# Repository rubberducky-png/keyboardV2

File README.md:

# keyboardV2: compact 61-key keyboard

A fully custom 61-key mechanical keyboard designed by me, including the PCB, case, firmware, and assembly.

Started With the Macondo Program and Finished with the Forge Program

## Features

- Custom PCB designed from scratch
- Hot-swappable MX-compatible switches
- ZMK firmware
- Screw-in stabilizers
- 3D printed two-piece tray mount case
- Switch plate
- PCB foam
- bluetooth
- RGB lights
  
## Why I Built It

I built another keyboard before this and ended up hating how it looked and how I desgined it. So I went back to the drawing board and decided to make one I would actually like.

## Design Process

The project began by selecting a 61-key layout that has a lot of function but is also on the smaller side. I then designed the PCB in KiCad, routed all the traces, and added support for hot-swap sockets and USB-C connectivity. After the electronics were complete I designed a simple tray mount in Onshape. The case is made out of two PLA printed pieces and includes a shelf for the pcb to rest on. Because of small bed size I will have to print them in pieces.

Finally, the keyboard will be flashed with VIA firmware

## Challenges

Some of the biggest challenges included:

- Learning PCB routing and keyboard matrix design
- Designing a printable case that was able to support the pcb well
- Ensuring all mounting points aligned correctly

## Images and Renders!

### Matrix Schematic

### OnShape Render
- assembly file is public at: https://cad.onshape.com/documents/9cbec0f54e40138e58fcc79a/w/808f2acb50a46c5c63af6f12/e/cd5daac02ca5b9e828f3d085

#### Case

### Switch Plate

### PCB

### Assembly

## Bill of Materials (BOM)

The following table lists the components required to build the custom 60% wireless mechanical keyboard.

| # | Component | Description | Quantity | Unit Price | Subtotal |
|---:|---|---|---:|---:|---:|
| 1 | [Glorious Fox Linear Switches](https://www.amazon.com/GLORIOUS-Linear-Mechanical-Switches-Keyboards/dp/B0D7QW8SQ9) | MX-compatible linear switches, 110-pack | 110 | $0.2272 | $24.99 |
| 2 | [Gateron PCB-Mounted Stabilizers](https://www.amazon.com/gp/product/B0BZYK3X1S) | PCB-mounted stabilizer set for larger keys | 1 set | $9.99 | $9.99 |
| 3 | [SuperMini nRF52840](https://www.amazon.com/AITRIP-Development-Bluetooth-Management-Module%EF%BC%8CNano/dp/B0DCZJKYL1) | Pro Micro alternative; Bluetooth LE and ZMK compatible | 1 | $13.99 | $13.99 |
| 4 | [SK6812MINI-E RGB LEDs](https://www.amazon.com/100PCS-Similar-WS2812B-Individually-Addressable/dp/B0DMNBBM9V) | Individually addressable per-key RGB LEDs, 100-pack | 100 | $0.15 | $15.46 |
| 5 | [Kailh Hot-Swap Sockets](https://www.amazon.com/Hot-swappable-Socket-CPG151101S11-Mechanical-Keyboard/dp/B096WZ6TJ5) | MX-compatible hot-swap sockets, 100-pack | 100 | $0.125 | $12.50 |
| 6 | [JLCPCB PCB Fabrication](https://jlcpcb.com) | Custom PCB manufacturing, 5 boards, including shipping | 1 order | — | $35.03 |
| 7 | [3.7V LiPo Battery](https://www.amazon.com/YTKavq-Battery-Lithium-Rechargeable-Connector/dp/B08TV4J9H7) | Rechargeable lithium polymer battery, approximately 1000mAh, JST-PH connector | 1 | $7.59 | $7.59 |
| 8 | [JST-PH 2.0mm Connector](https://www.amazon.com/JST-PH-Connector-Silicone-Cables-Female/dp/B0F9PD2LPW) | 2-pin battery connector with silicone wiring | 1 | $5.99 | $5.99 |
| 9 | [SPDT Slide Switch](https://www.amazon.com/gp/product/B0DN67RV4W) | Power on/off switch, 2.54mm pin spacing | 1 | $6.99 | $6.99 |
| 10 | [Momentary Tactile Push Button](https://www.amazon.com/Momentary-Tactile-Switches-Through-Breadboard/dp/B0G5Q9RPJW) | Reset button | 1 | $5.99 | $5.99 |
| 11 | [Womier Double-Shot PBT Keycaps](https://www.amazon.com/Keycaps-Doubleshot-Percent-Mechanical-Keyboard/dp/B0DDC6PNY6) | Cherry-profile double-shot PBT keycap set | 1 set | $17.99 | $17.99 |
| 12 | [22µF 0805 MLCC Capacitors](https://www.amazon.com/Chip-Capacitor-MLCC-22uF-CS2012X5R226M250NRE/dp/B096WDCLWY) | X5R ceramic capacitors for power filtering, 10-pack | 10 | $0.499 | $4.99 |
| 13 | [CHANZON 100nF 0805 Capacitors](https://www.amazon.com/CHANZON-100nF-Ceramic-Capacitor-100pcs/dp/B0GWH4RRQS) | LED decoupling capacitors, 100-pack | 100 | $0.076 | $7.60 |
| 14 | [0805 SMD Resistors 470 ohms](https://www.amazon.com/HiLetgo-Values-Resistors-Assortment-Resistor/dp/B07R5S5RFK/ref=sr_1_1_sspa?dib=eyJ2IjoiMSJ9.QrbL5hsl3y3O6gmstmy_4ZD0PpMRLFJ7NhmAE3dIEMUj69VnxSscBgx1Y_NvgiuXhPPsI573Q7wFUPvs_THPc2HkjAqAmswXhBcCxd4afR0o-SfQNniGOnE40pkLAjc971XgZG_Vreq0zhsYtezMDwFAChPOIei81v4d8d9fdSgrF1oYQbbqwz3Tw8FshrM3dyWXSGyEhGIDRhhHlnimh7bHPPrxl0DcY0hEvuhDMCE.ricUM_RpbJ0mivxPTOZyA8MBNaog89FuJmiqJ4fPW4c&dib_tag=se&keywords=450+ohm+0805+SMD+resistor&qid=1794352900&sr=8-1-spons&sp_csd=d2lkZ2V0TmFtZT1zcF9hdGY&psc=1) | 0805 resistors, 400 pack | 400 | | $6.89

### Cost Summary

| Category | Cost |
|---|---:|
| Components and hardware | $140.96 |
| PCB fabrication and shipping | $35.03 |
| **Total Project Cost** | **$175.99** |

*Prices are based on the listed purchase prices and may change. The PCB cost includes manufacturing and shipping.*

### Project Notes
- Keyboard layout: 60% ANSI.
- Connectivity: Bluetooth Low Energy (BLE).
- Firmware: ZMK.
- Switch compatibility: Cherry MX-style mechanical switches.
- Switch mounting: MX hot-swap sockets.
- Lighting: Individually addressable per-key RGB using SK6812MINI-E LEDs.
- Battery: Rechargeable 3.7V lithium polymer cell.
- Layers: Two firmware layers, with Right Alt configured as the Fn key.

## Shoutout hackclub and the macondo program

</center>

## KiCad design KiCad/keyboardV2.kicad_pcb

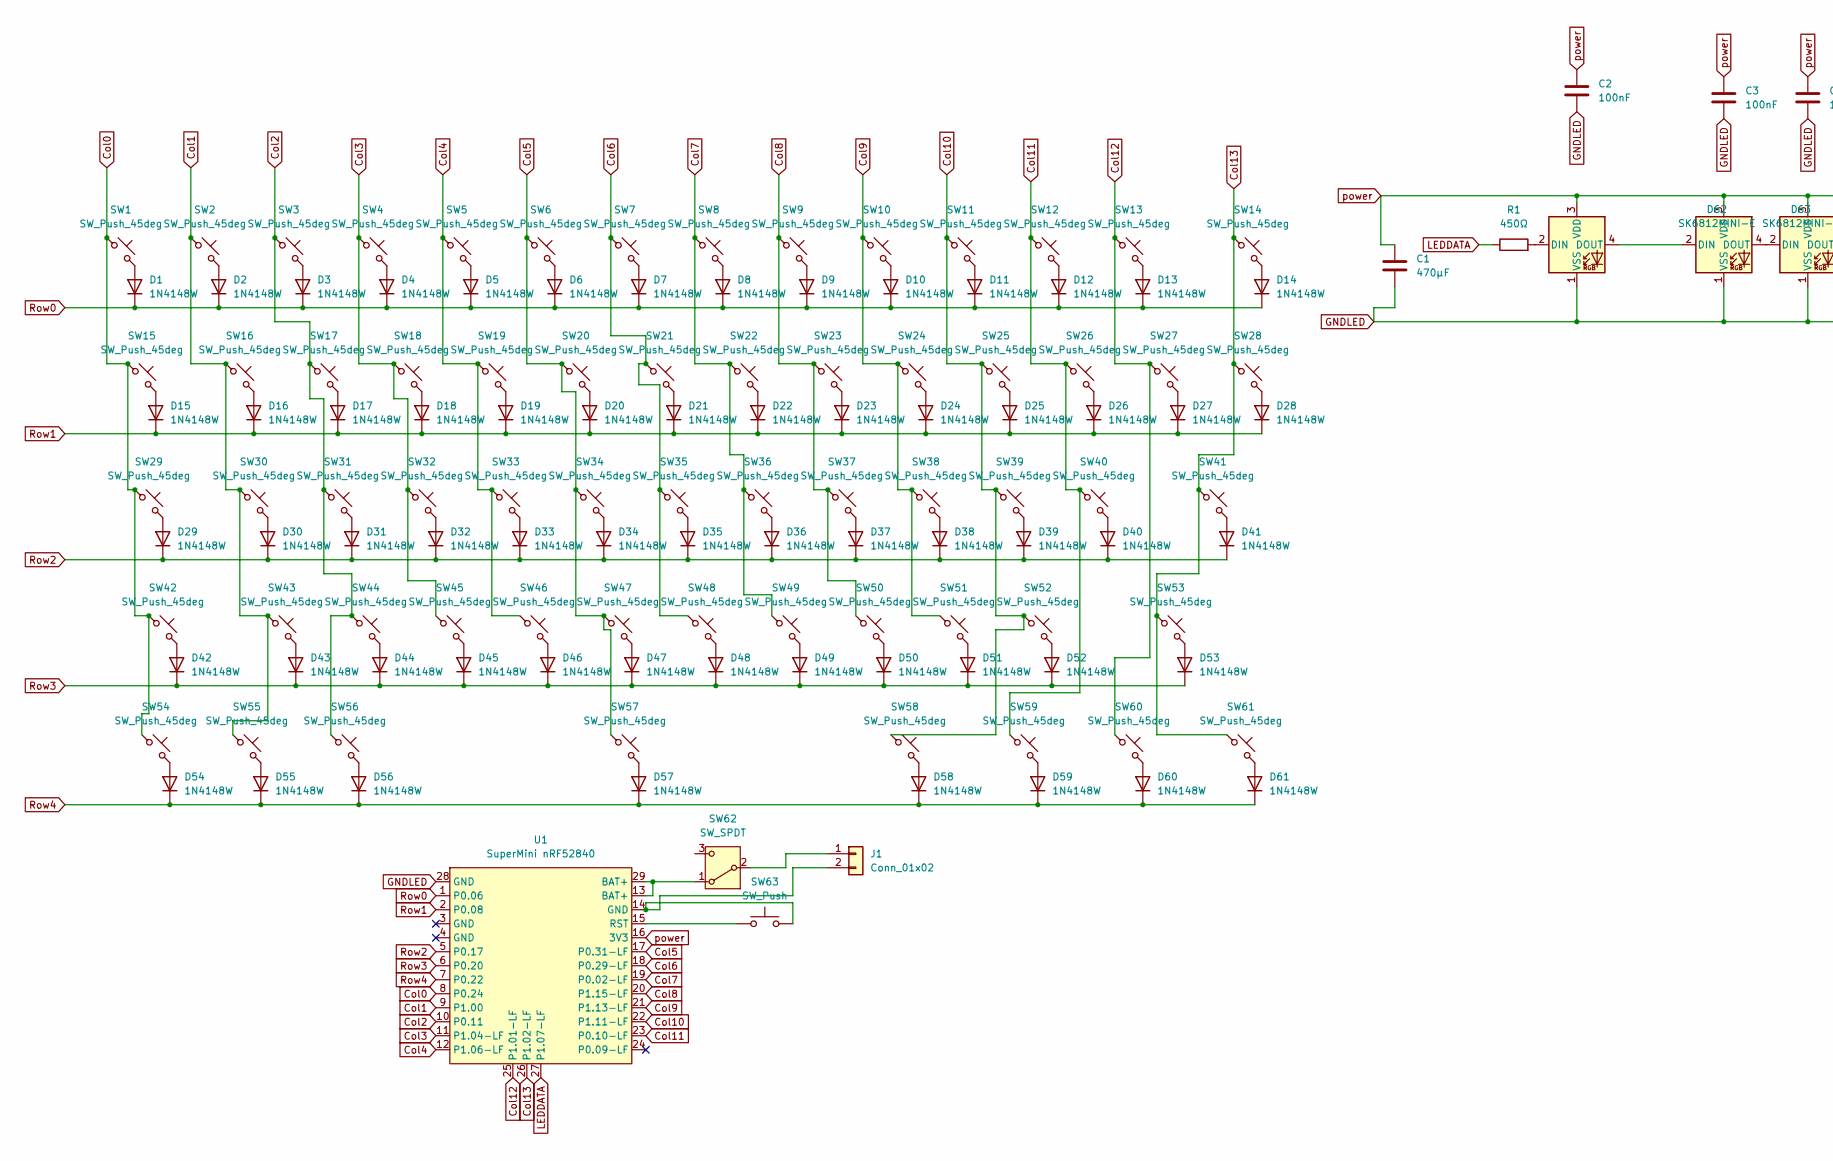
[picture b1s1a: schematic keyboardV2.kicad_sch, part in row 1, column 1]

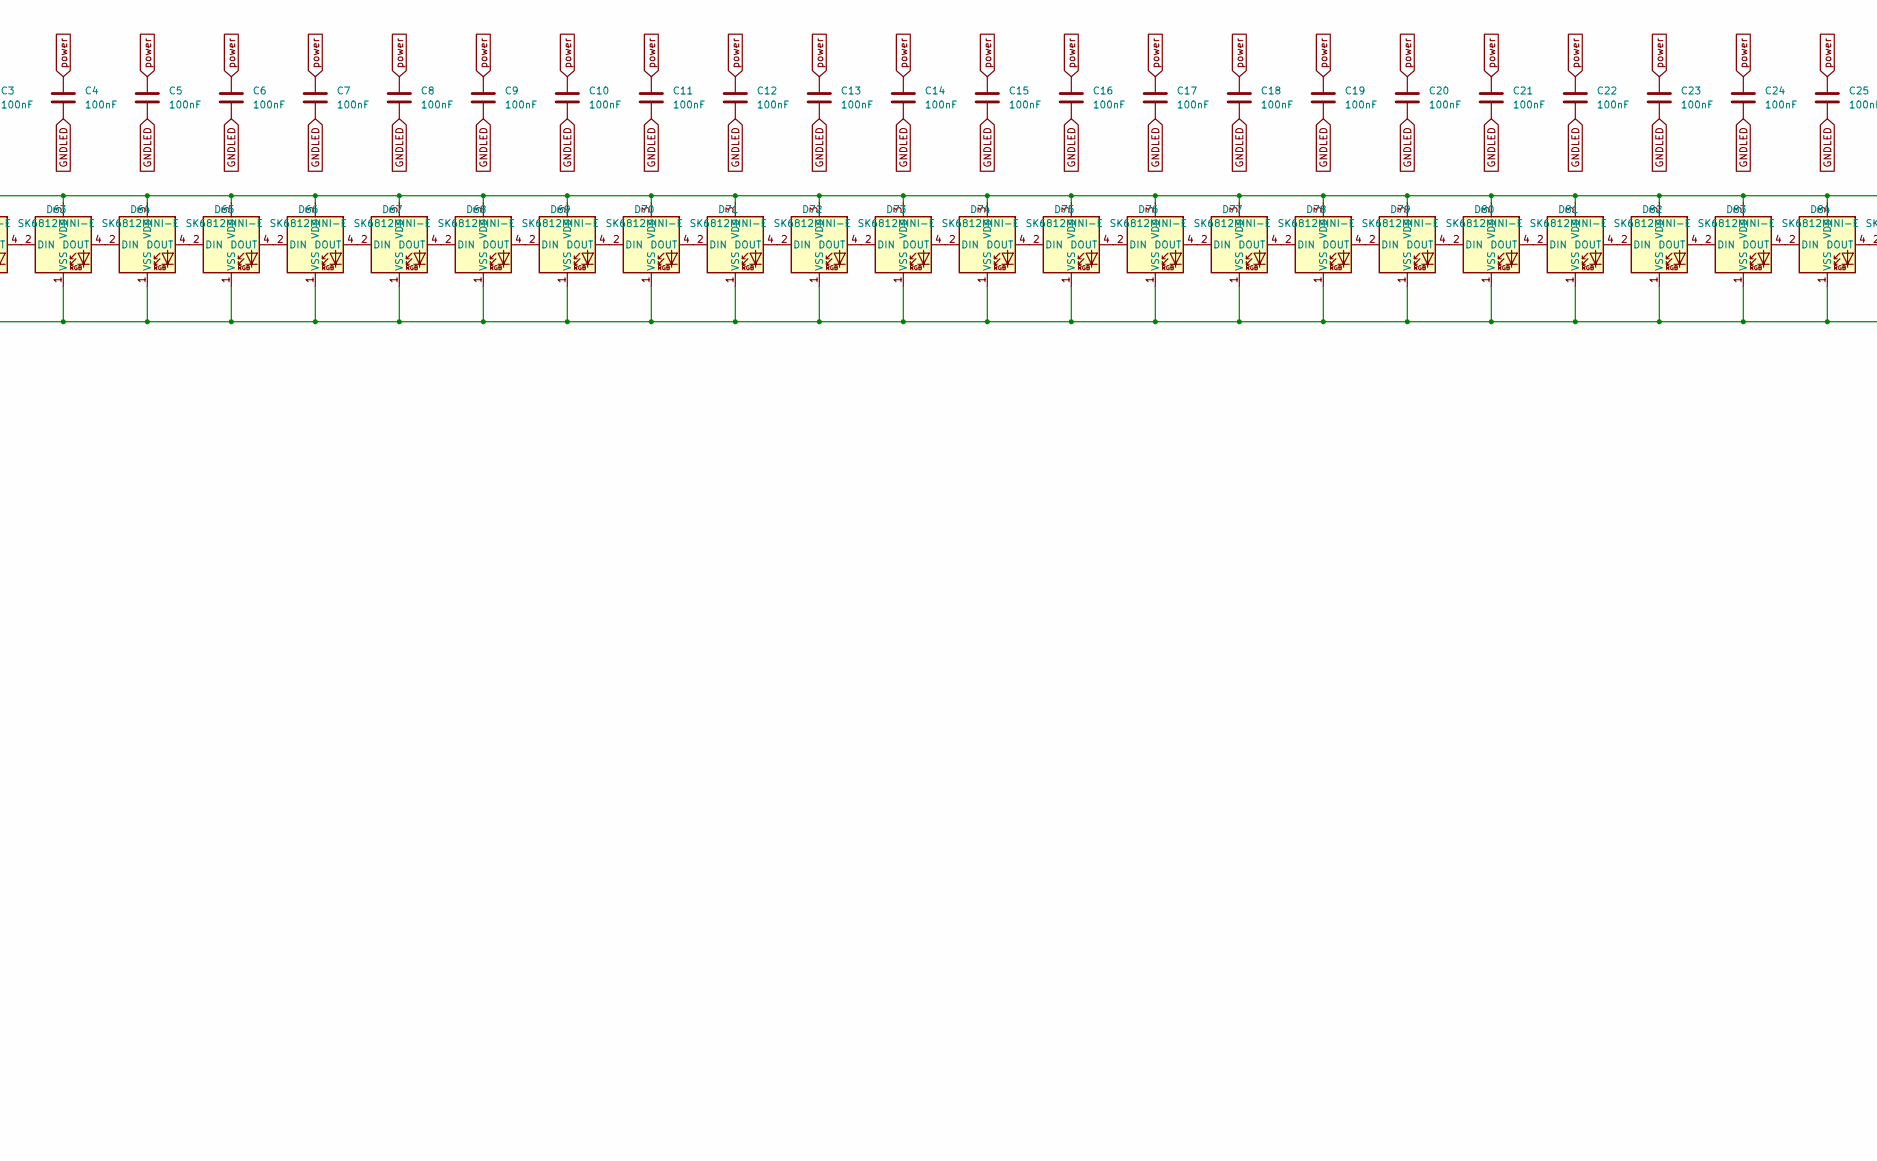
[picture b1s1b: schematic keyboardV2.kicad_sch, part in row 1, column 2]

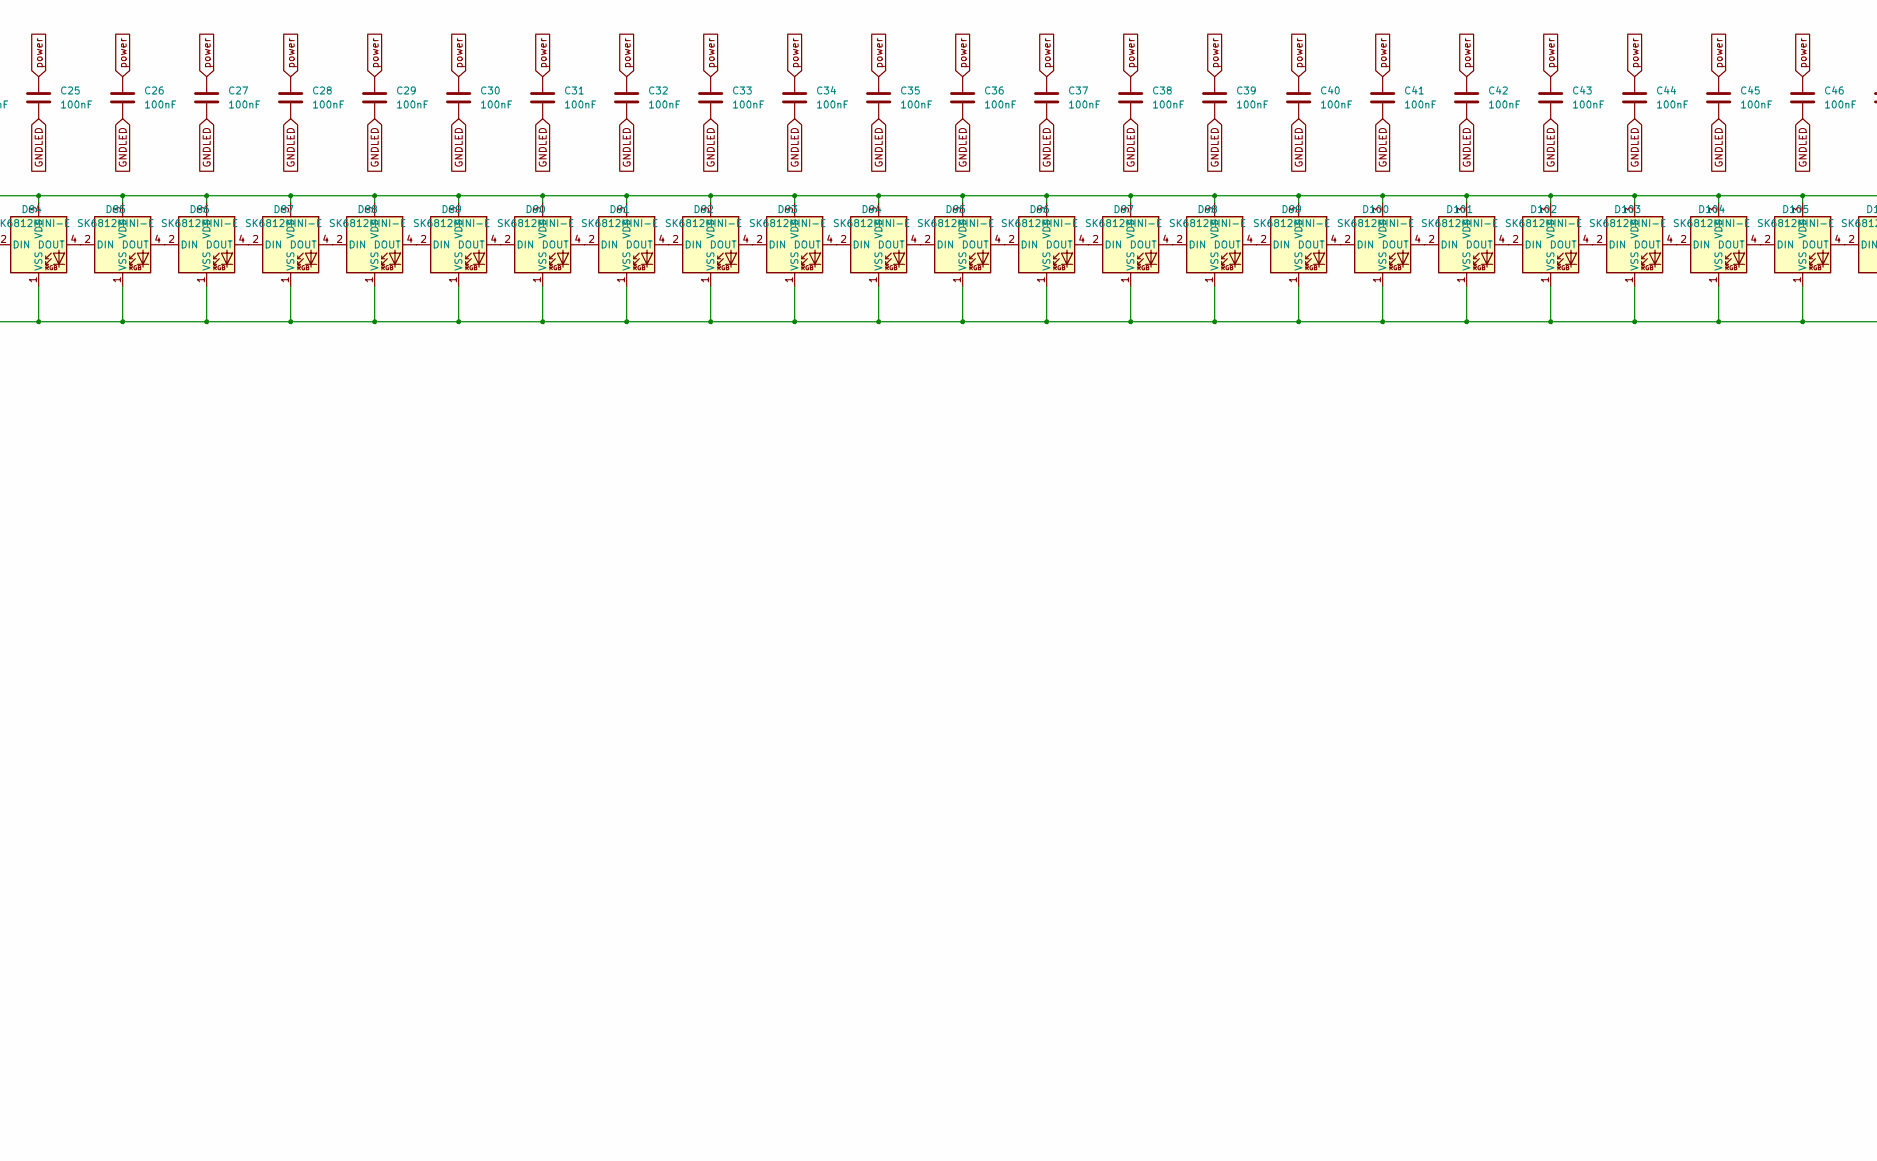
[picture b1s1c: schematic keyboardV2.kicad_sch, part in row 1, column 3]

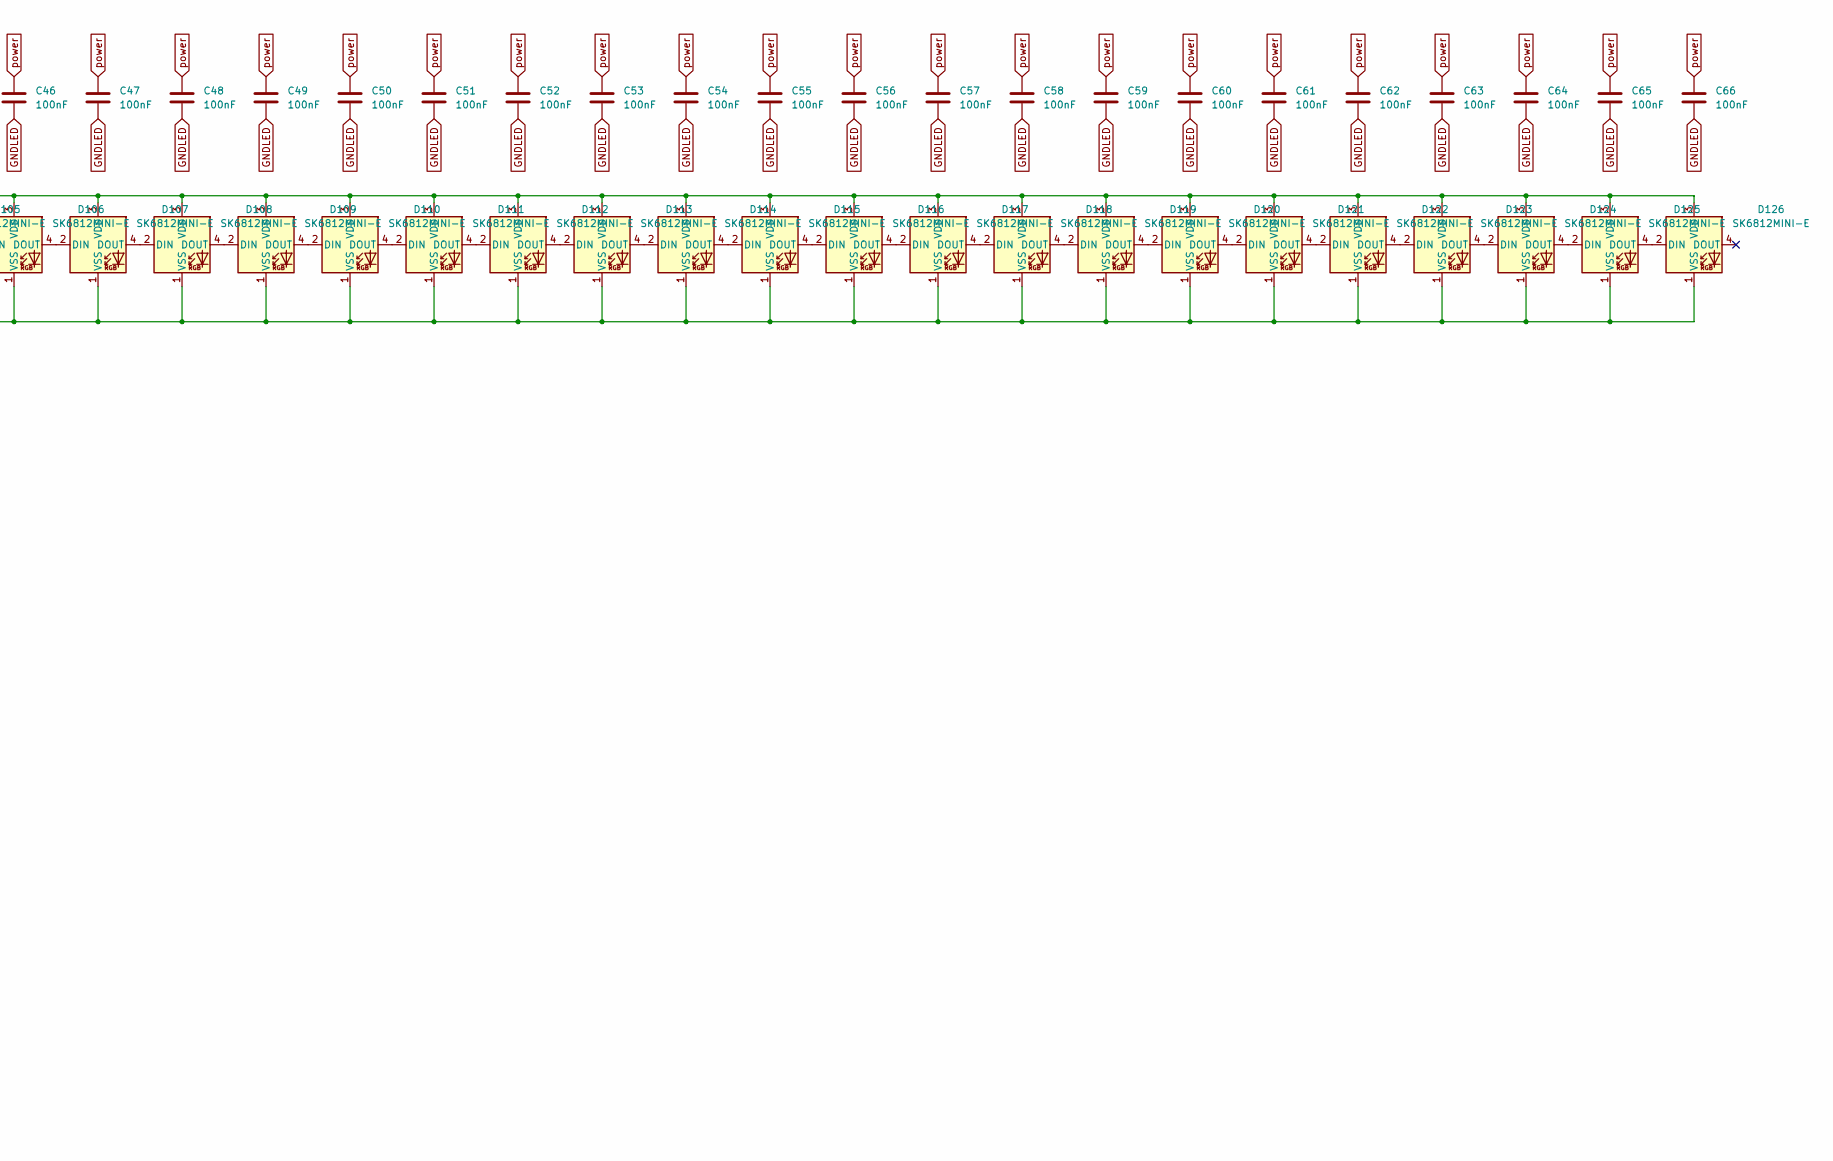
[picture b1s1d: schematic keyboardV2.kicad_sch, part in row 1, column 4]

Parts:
C1: 470µF; C_0805_2012Metric
C2, C3, C4, C5, C6, C7, C8, C9, C10, C11, C12, C13, C14, C15, C16, C17, C18, C19, C20, C21, C22, C23, C24, C25, C26, C27, C28, C29, C30, C31, C32, C33, C34, C35, C36, C37, C38, C39, C40, C41, C42, C43, C44, C45, C46, C47, C48, C49, C50, C51, C52, C53, C54, C55, C56, C57, C58, C59, C60, C61, C62, C63, C64, C65, C66: 100nF; C_0805_2012Metric
D1, D2, D3, D4, D5, D6, D7, D8, D9, D10, D11, D12, D13, D14, D15, D16, D17, D18, D19, D20, D21, D22, D23, D24, D25, D26, D27, D28, D29, D30, D31, D32, D33, D34, D35, D36, D37, D38, D39, D40, D41, D42, D43, D44, D45, D46, D47, D48, D49, D50, D51, D52, D53, D54, D55, D56, D57, D58, D59, D60, D61: 1N4148W; D_SOD-123
D62, D63, D64, D65, D66, D67, D68, D69, D70, D71, D72, D73, D74, D75, D76, D77, D78, D79, D80, D81, D82, D83, D84, D85, D86, D87, D88, D89, D90, D91, D92, D93, D94, D95, D96, D97, D98, D99, D100, D101, D102, D103, D104, D105, D106, D107, D108, D109, D110, D111, D112, D113, D114, D115, D116, D117, D118, D119, D120, D121, D122, D123, D124, D125, D126: SK6812MINI-E; LED_SK6812MINI-E_3.2x2.8mm_P1.5mm_ReverseMount
J1: Conn_01x02; JST_PH_S2B-PH-K_1x02_P2.00mm_Horizontal
R1: 450Ω; R_0805_2012Metric
SW1, SW2, SW3, SW4, SW5, SW6, SW7, SW8, SW9, SW10, SW11, SW12, SW13, SW16, SW17, SW18, SW19, SW20, SW21, SW22, SW23, SW24, SW25, SW26, SW27, SW30, SW31, SW32, SW33, SW34, SW35, SW36, SW37, SW38, SW39, SW40, SW43, SW44, SW45, SW46, SW47, SW48, SW49, SW50, SW51, SW52, SW59, SW60, SW61: SW_Push_45deg; MX-Hotswap-1U
SW14: SW_Push_45deg; MX-Hotswap-2U
SW15, SW28, SW54, SW58: SW_Push_45deg; MX-Hotswap-1.5U
SW29: SW_Push_45deg; MX-Hotswap-1.75U
SW41, SW42: SW_Push_45deg; MX-Hotswap-2.25U
SW53: SW_Push_45deg; MX-Hotswap-2.75U
SW55, SW56: SW_Push_45deg; MX-Hotswap-1.25U
SW57: SW_Push_45deg; MX-Hotswap-6.25U
SW62: SW_SPDT; SW_SPDT_CK_JS102011SAQN
SW63: SW_Push; SW_SPST_B3U-3100P-B
U1: SuperMini nRF52840; SuperMini NRF52840

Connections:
Col0: SW1.1, SW15.1, SW29.1, SW42.1, SW54.1, U1.8 (P0.24)
Col1: SW2.1, SW16.1, SW30.1, SW43.1, SW55.1, U1.9 (P1.00)
Col2: SW3.1, SW17.1, SW31.1, SW44.1, SW56.1, U1.10 (P0.11)
Col3: SW4.1, SW18.1, SW32.1, SW45.1, U1.11 (P1.04-LF)
Col4: SW5.1, SW19.1, SW33.1, SW46.1, U1.12 (P1.06-LF)
Col5: SW6.1, SW20.1, SW34.1, SW47.1, SW57.1, U1.17 (P0.31-LF)
Col6: SW7.1, SW21.1, SW35.1, SW48.1, U1.18 (P0.29-LF)
Col7: SW8.1, SW22.1, SW36.1, SW49.1, U1.19 (P0.02-LF)
Col8: SW9.1, SW23.1, SW37.1, SW50.1, U1.20 (P1.15-LF)
Col9: SW10.1, SW24.1, SW38.1, SW51.1, U1.21 (P1.13-LF)
Col10: SW11.1, SW25.1, SW39.1, SW52.1, SW58.1, U1.22 (P1.11-LF)
Col11: SW12.1, SW26.1, SW40.1, SW59.1, U1.23 (P0.10-LF)
Col12: SW13.1, SW27.1, SW60.1, U1.25 (P1.01-LF)
Col13: SW14.1, SW28.1, SW41.1, SW53.1, SW61.1, U1.26 (P1.02-LF)
GNDLED: C1.1, C2.1, C3.1, C4.1, C5.1, C6.1, C7.1, C8.1, C9.1, C10.1, C11.1, C12.1, C13.1, C14.1, C15.1, C16.1, C17.1, C18.1, C19.1, C20.1, C21.1, C22.1, C23.1, C24.1, C25.1, C26.1, C27.1, C28.1, C29.1, C30.1, C31.1, C32.1, C33.1, C34.1, C35.1, C36.1, C37.1, C38.1, C39.1, C40.1, C41.1, C42.1, C43.1, C44.1, C45.1, C46.1, C47.1, C48.1, C49.1, C50.1, C51.1, C52.1, C53.1, C54.1, C55.1, C56.1, C57.1, C58.1, C59.1, C60.1, C61.1, C62.1, C63.1, C64.1, C65.1, C66.1, D62.1 (VSS), D63.1 (VSS), D64.1 (VSS), D65.1 (VSS), D66.1 (VSS), D67.1 (VSS), D68.1 (VSS), D69.1 (VSS), D70.1 (VSS), D71.1 (VSS), D72.1 (VSS), D73.1 (VSS), D74.1 (VSS), D75.1 (VSS), D76.1 (VSS), D77.1 (VSS), D78.1 (VSS), D79.1 (VSS), D80.1 (VSS), D81.1 (VSS), D82.1 (VSS), D83.1 (VSS), D84.1 (VSS), D85.1 (VSS), D86.1 (VSS), D87.1 (VSS), D88.1 (VSS), D89.1 (VSS), D90.1 (VSS), D91.1 (VSS), D92.1 (VSS), D93.1 (VSS), D94.1 (VSS), D95.1 (VSS), D96.1 (VSS), D97.1 (VSS), D98.1 (VSS), D99.1 (VSS), D100.1 (VSS), D101.1 (VSS), D102.1 (VSS), D103.1 (VSS), D104.1 (VSS), D105.1 (VSS), D106.1 (VSS), D107.1 (VSS), D108.1 (VSS), D109.1 (VSS), D110.1 (VSS), D111.1 (VSS), D112.1 (VSS), D113.1 (VSS), D114.1 (VSS), D115.1 (VSS), D116.1 (VSS), D117.1 (VSS), D118.1 (VSS), D119.1 (VSS), D120.1 (VSS), D121.1 (VSS), D122.1 (VSS), D123.1 (VSS), D124.1 (VSS), D125.1 (VSS), D126.1 (VSS), U1.28 (GND)
LEDDATA: R1.1, U1.27 (P1.07-LF)
unnamed: D1.2 (A), SW1.2
unnamed: D2.2 (A), SW2.2
unnamed: D3.2 (A), SW3.2
unnamed: D4.2 (A), SW4.2
unnamed: D5.2 (A), SW5.2
unnamed: D6.2 (A), SW6.2
unnamed: D7.2 (A), SW7.2
unnamed: D8.2 (A), SW8.2
unnamed: D9.2 (A), SW9.2
unnamed: D10.2 (A), SW10.2
unnamed: D11.2 (A), SW11.2
unnamed: D12.2 (A), SW12.2
unnamed: D13.2 (A), SW13.2
unnamed: D14.2 (A), SW14.2
unnamed: D15.2 (A), SW15.2
unnamed: D16.2 (A), SW16.2
unnamed: D17.2 (A), SW17.2
unnamed: D18.2 (A), SW18.2
unnamed: D19.2 (A), SW19.2
unnamed: D20.2 (A), SW20.2
unnamed: D21.2 (A), SW21.2
unnamed: D22.2 (A), SW22.2
unnamed: D23.2 (A), SW23.2
unnamed: D24.2 (A), SW24.2
unnamed: D25.2 (A), SW25.2
unnamed: D26.2 (A), SW26.2
unnamed: D27.2 (A), SW27.2
unnamed: D28.2 (A), SW28.2
unnamed: D29.2 (A), SW29.2
unnamed: D30.2 (A), SW30.2
unnamed: D31.2 (A), SW31.2
unnamed: D32.2 (A), SW32.2
unnamed: D33.2 (A), SW33.2
unnamed: D34.2 (A), SW34.2
unnamed: D35.2 (A), SW35.2
unnamed: D36.2 (A), SW36.2
unnamed: D37.2 (A), SW37.2
unnamed: D38.2 (A), SW38.2
unnamed: D39.2 (A), SW39.2
unnamed: D40.2 (A), SW40.2
unnamed: D41.2 (A), SW41.2
unnamed: D42.2 (A), SW42.2
unnamed: D43.2 (A), SW43.2
unnamed: D44.2 (A), SW44.2
unnamed: D45.2 (A), SW45.2
unnamed: D46.2 (A), SW46.2
unnamed: D47.2 (A), SW47.2
unnamed: D48.2 (A), SW48.2
unnamed: D49.2 (A), SW49.2
unnamed: D50.2 (A), SW50.2
unnamed: D51.2 (A), SW51.2
unnamed: D52.2 (A), SW52.2
unnamed: D53.2 (A), SW53.2
unnamed: D54.2 (A), SW54.2
unnamed: D55.2 (A), SW55.2
unnamed: D56.2 (A), SW56.2
unnamed: D57.2 (A), SW57.2
unnamed: D58.2 (A), SW58.2
unnamed: D59.2 (A), SW59.2
unnamed: D60.2 (A), SW60.2
unnamed: D61.2 (A), SW61.2
unnamed: D62.2 (DIN), R1.2
unnamed: D62.4 (DOUT), D63.2 (DIN)
unnamed: D63.4 (DOUT), D64.2 (DIN)
unnamed: D64.4 (DOUT), D65.2 (DIN)
unnamed: D65.4 (DOUT), D66.2 (DIN)
unnamed: D66.4 (DOUT), D67.2 (DIN)
unnamed: D67.4 (DOUT), D68.2 (DIN)
unnamed: D68.4 (DOUT), D69.2 (DIN)
unnamed: D69.4 (DOUT), D70.2 (DIN)
unnamed: D70.4 (DOUT), D71.2 (DIN)
unnamed: D71.4 (DOUT), D72.2 (DIN)
unnamed: D72.4 (DOUT), D73.2 (DIN)
unnamed: D73.4 (DOUT), D74.2 (DIN)
unnamed: D74.4 (DOUT), D75.2 (DIN)
unnamed: D75.4 (DOUT), D76.2 (DIN)
unnamed: D76.4 (DOUT), D77.2 (DIN)
unnamed: D77.4 (DOUT), D78.2 (DIN)
unnamed: D78.4 (DOUT), D79.2 (DIN)
unnamed: D79.4 (DOUT), D80.2 (DIN)
unnamed: D80.4 (DOUT), D81.2 (DIN)
unnamed: D81.4 (DOUT), D82.2 (DIN)
unnamed: D82.4 (DOUT), D83.2 (DIN)
unnamed: D83.4 (DOUT), D84.2 (DIN)
unnamed: D84.4 (DOUT), D85.2 (DIN)
unnamed: D85.4 (DOUT), D86.2 (DIN)
unnamed: D86.4 (DOUT), D87.2 (DIN)
unnamed: D87.4 (DOUT), D88.2 (DIN)
unnamed: D88.4 (DOUT), D89.2 (DIN)
unnamed: D89.4 (DOUT), D90.2 (DIN)
unnamed: D90.4 (DOUT), D91.2 (DIN)
unnamed: D91.4 (DOUT), D92.2 (DIN)
unnamed: D92.4 (DOUT), D93.2 (DIN)
unnamed: D93.4 (DOUT), D94.2 (DIN)
unnamed: D94.4 (DOUT), D95.2 (DIN)
unnamed: D95.4 (DOUT), D96.2 (DIN)
unnamed: D96.4 (DOUT), D97.2 (DIN)
unnamed: D97.4 (DOUT), D98.2 (DIN)
unnamed: D98.4 (DOUT), D99.2 (DIN)
unnamed: D99.4 (DOUT), D100.2 (DIN)
unnamed: D100.4 (DOUT), D101.2 (DIN)
unnamed: D101.4 (DOUT), D102.2 (DIN)
unnamed: D102.4 (DOUT), D103.2 (DIN)
unnamed: D103.4 (DOUT), D104.2 (DIN)
unnamed: D104.4 (DOUT), D105.2 (DIN)
unnamed: D105.4 (DOUT), D106.2 (DIN)
unnamed: D106.4 (DOUT), D107.2 (DIN)
unnamed: D107.4 (DOUT), D108.2 (DIN)
unnamed: D108.4 (DOUT), D109.2 (DIN)
unnamed: D109.4 (DOUT), D110.2 (DIN)
unnamed: D110.4 (DOUT), D111.2 (DIN)
unnamed: D111.4 (DOUT), D112.2 (DIN)
unnamed: D112.4 (DOUT), D113.2 (DIN)
unnamed: D113.4 (DOUT), D114.2 (DIN)
unnamed: D114.4 (DOUT), D115.2 (DIN)
unnamed: D115.4 (DOUT), D116.2 (DIN)
unnamed: D116.4 (DOUT), D117.2 (DIN)
unnamed: D117.4 (DOUT), D118.2 (DIN)
unnamed: D118.4 (DOUT), D119.2 (DIN)
unnamed: D119.4 (DOUT), D120.2 (DIN)
unnamed: D120.4 (DOUT), D121.2 (DIN)
unnamed: D121.4 (DOUT), D122.2 (DIN)
unnamed: D122.4 (DOUT), D123.2 (DIN)
unnamed: D123.4 (DOUT), D124.2 (DIN)
unnamed: D124.4 (DOUT), D125.2 (DIN)
unnamed: D125.4 (DOUT), D126.2 (DIN)
unnamed: J1.1, SW62.2 (B)
unnamed: J1.2, SW63.2, U1.14 (GND)
unnamed: SW62.1 (A), U1.13 (BAT+), U1.29 (BAT+)
unnamed: SW63.1, U1.15 (RST)
Row0: D1.1 (K), D2.1 (K), D3.1 (K), D4.1 (K), D5.1 (K), D6.1 (K), D7.1 (K), D8.1 (K), D9.1 (K), D10.1 (K), D11.1 (K), D12.1 (K), D13.1 (K), D14.1 (K), U1.1 (P0.06)
Row1: D15.1 (K), D16.1 (K), D17.1 (K), D18.1 (K), D19.1 (K), D20.1 (K), D21.1 (K), D22.1 (K), D23.1 (K), D24.1 (K), D25.1 (K), D26.1 (K), D27.1 (K), D28.1 (K), U1.2 (P0.08)
Row2: D29.1 (K), D30.1 (K), D31.1 (K), D32.1 (K), D33.1 (K), D34.1 (K), D35.1 (K), D36.1 (K), D37.1 (K), D38.1 (K), D39.1 (K), D40.1 (K), D41.1 (K), U1.5 (P0.17)
Row3: D42.1 (K), D43.1 (K), D44.1 (K), D45.1 (K), D46.1 (K), D47.1 (K), D48.1 (K), D49.1 (K), D50.1 (K), D51.1 (K), D52.1 (K), D53.1 (K), U1.6 (P0.20)
Row4: D54.1 (K), D55.1 (K), D56.1 (K), D57.1 (K), D58.1 (K), D59.1 (K), D60.1 (K), D61.1 (K), U1.7 (P0.22)
power: C1.2, C2.2, C3.2, C4.2, C5.2, C6.2, C7.2, C8.2, C9.2, C10.2, C11.2, C12.2, C13.2, C14.2, C15.2, C16.2, C17.2, C18.2, C19.2, C20.2, C21.2, C22.2, C23.2, C24.2, C25.2, C26.2, C27.2, C28.2, C29.2, C30.2, C31.2, C32.2, C33.2, C34.2, C35.2, C36.2, C37.2, C38.2, C39.2, C40.2, C41.2, C42.2, C43.2, C44.2, C45.2, C46.2, C47.2, C48.2, C49.2, C50.2, C51.2, C52.2, C53.2, C54.2, C55.2, C56.2, C57.2, C58.2, C59.2, C60.2, C61.2, C62.2, C63.2, C64.2, C65.2, C66.2, D62.3 (VDD), D63.3 (VDD), D64.3 (VDD), D65.3 (VDD), D66.3 (VDD), D67.3 (VDD), D68.3 (VDD), D69.3 (VDD), D70.3 (VDD), D71.3 (VDD), D72.3 (VDD), D73.3 (VDD), D74.3 (VDD), D75.3 (VDD), D76.3 (VDD), D77.3 (VDD), D78.3 (VDD), D79.3 (VDD), D80.3 (VDD), D81.3 (VDD), D82.3 (VDD), D83.3 (VDD), D84.3 (VDD), D85.3 (VDD), D86.3 (VDD), D87.3 (VDD), D88.3 (VDD), D89.3 (VDD), D90.3 (VDD), D91.3 (VDD), D92.3 (VDD), D93.3 (VDD), D94.3 (VDD), D95.3 (VDD), D96.3 (VDD), D97.3 (VDD), D98.3 (VDD), D99.3 (VDD), D100.3 (VDD), D101.3 (VDD), D102.3 (VDD), D103.3 (VDD), D104.3 (VDD), D105.3 (VDD), D106.3 (VDD), D107.3 (VDD), D108.3 (VDD), D109.3 (VDD), D110.3 (VDD), D111.3 (VDD), D112.3 (VDD), D113.3 (VDD), D114.3 (VDD), D115.3 (VDD), D116.3 (VDD), D117.3 (VDD), D118.3 (VDD), D119.3 (VDD), D120.3 (VDD), D121.3 (VDD), D122.3 (VDD), D123.3 (VDD), D124.3 (VDD), D125.3 (VDD), D126.3 (VDD), U1.16 (3V3)

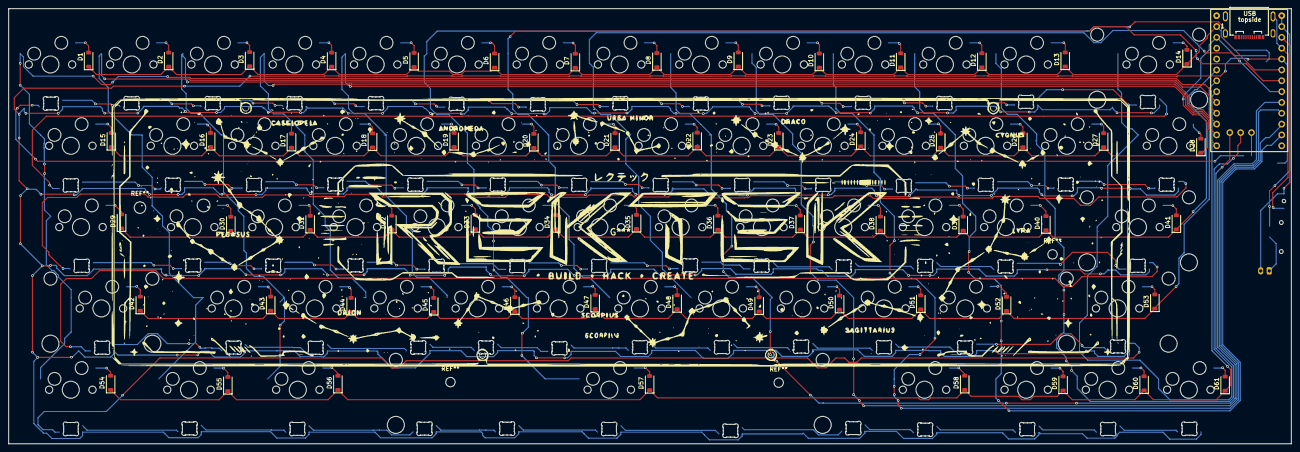
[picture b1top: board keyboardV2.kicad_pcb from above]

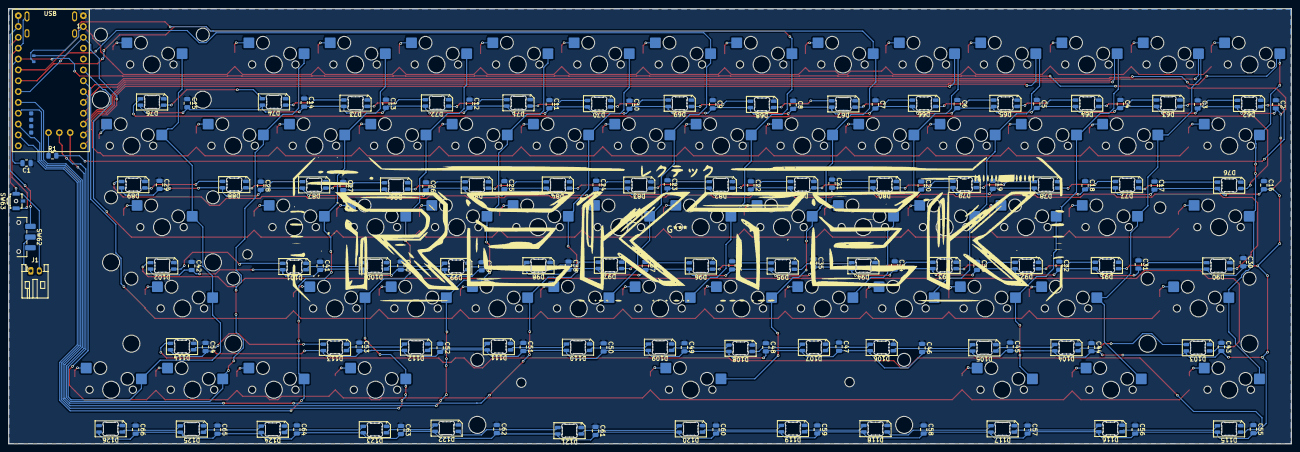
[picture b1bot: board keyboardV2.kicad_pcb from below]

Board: 2 copper layers, 300.5 x 101.9 mm, 258 parts (196 on the bottom side), 152 nets.
